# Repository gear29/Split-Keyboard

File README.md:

# Split-Keyboard
This is a key board  but 2
firm ware https://github.com/gear29/wireless-split-keyboard-firmware

 Wireless Split Keyboard

A custom wireless split mechanical keyboard powered by two Seeed Studio XIAO nRF52840 controllers and ZMK firmware.

Project Overview

Wireless Split Keyboard is a custom split keyboard designed around two independently powered wireless halves. Each half uses a Seeed Studio XIAO nRF52840 microcontroller and communicates using ZMK's split keyboard functionality.

The goal of this project is to create a fully custom keyboard, including its PCB, firmware, and mechanical design.

Features

Wireless split keyboard design

Two Seeed Studio XIAO nRF52840 controllers

ZMK firmware

Custom 5×5 matrix per half

42 total keys

Mechanical keyboard switches

Custom PCB design

Configurable keymap and layers

Repository Structure

wireless-split-keyboard/
├── README.md
├── bom.csv
├── PCB/
│   ├── schematic.kicad_sch
│   ├── pcb.kicad_pcb
│   └── gerbers/
├── CAD/
│   └── source-files/
└── Firmware/
    └── ZMK firmware repository

Building

Manufacture the custom PCB.

Assemble the keyboard electronics.

Flash the left and right ZMK firmware.

Configure and test the keyboard.

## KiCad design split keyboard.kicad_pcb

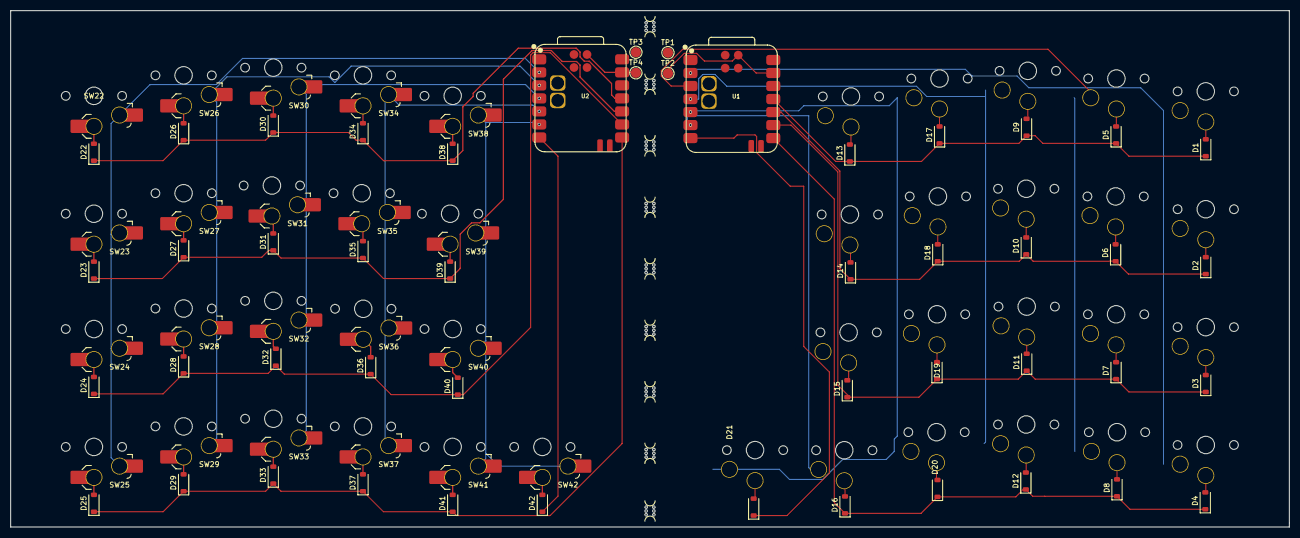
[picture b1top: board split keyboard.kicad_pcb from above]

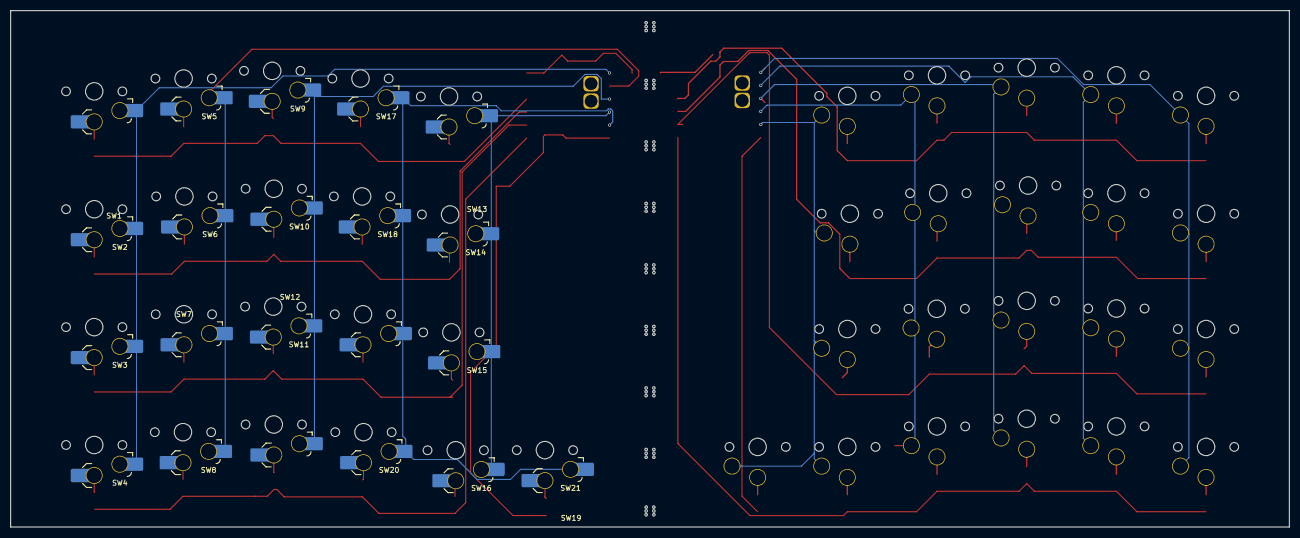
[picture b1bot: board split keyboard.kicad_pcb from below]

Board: 2 copper layers, 249.5 x 100.8 mm, 99 parts (21 on the bottom side), 64 nets.

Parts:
B1, B2, B3, B4, B5, B6, B8, B9, B10: MouseBite; mouse-bite-2mm-slot
D1, D2, D3, D4, D5, D6, D7, D8, D9, D10, D11, D12, D13, D14, D15, D16, D17, D18, D19, D20, D21, D22, D23, D24, D25, D26, D27, D28, D29, D30, D31, D32, D33, D34, D35, D36, D37, D38, D39, D40, D41, D42: D; D_SOD-123
SW1, SW2, SW3, SW4, SW5, SW6, SW7, SW8, SW9, SW10, SW11, SW12, SW13, SW14, SW15, SW16, SW17, SW18, SW19, SW20, SW21, SW22, SW23, SW24, SW25, SW26, SW27, SW28, SW29, SW30, SW31, SW32, SW33, SW34, SW35, SW36, SW37, SW38, SW39, SW40, SW41, SW42: SW_Push; SW_choc_v1_HS_CPG135001S30_1.5u
TP1, TP3: bat; TestPoint_Pad_D2.0mm
TP2, TP4: gnd; TestPoint_Pad_D2.0mm
U1, U2: XIAO-nRF52840-SMD; modified-XIAO-nRF52840-SMD

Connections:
/left(page 2)/C0L0: SW1.1, SW2.1, SW3.1, SW4.1, U1.2 (D1)
/left(page 2)/C0L1: SW5.1, SW6.1, SW7.1, SW8.1, U1.3 (D2)
/left(page 2)/C0L2: SW9.1, SW10.1, SW11.1, SW12.1, U1.4 (D3)
/left(page 2)/C0L3: SW13.1, SW14.1, SW15.1, SW16.1, U1.5 (D4)
/left(page 2)/C0L4: SW17.1, SW18.1, SW19.1, SW20.1, SW21.1, U1.6 (D5)
/left(page 2)/R0W0: D1.1 (K), D5.1 (K), D9.1 (K), D13.1 (K), D17.1 (K), U1.11 (D10)
/left(page 2)/R0W1: D2.1 (K), D6.1 (K), D10.1 (K), D14.1 (K), D18.1 (K), U1.10 (D9)
/left(page 2)/R0W2: D3.1 (K), D7.1 (K), D11.1 (K), D15.1 (K), D19.1 (K), U1.9 (D8)
/left(page 2)/R0W3: D4.1 (K), D8.1 (K), D12.1 (K), D16.1 (K), D20.1 (K), U1.8 (D7)
/left(page 2)/R0W4: D21.1 (K), U1.7 (D6)
/right/C0L0: SW22.1, SW23.1, SW24.1, SW25.1, U2.2 (D1)
/right/C0L1: SW26.1, SW27.1, SW28.1, SW29.1, U2.3 (D2)
/right/C0L2: SW30.1, SW31.1, SW32.1, SW33.1, U2.4 (D3)
/right/C0L3: SW34.1, SW35.1, SW36.1, SW37.1, U2.5 (D4)
/right/C0L4: SW38.1, SW39.1, SW40.1, SW41.1, SW42.1, U2.6 (D5)
/right/R0W0: D22.1 (K), D26.1 (K), D30.1 (K), D34.1 (K), D38.1 (K), U2.11 (D10)
/right/R0W1: D23.1 (K), D27.1 (K), D31.1 (K), D35.1 (K), D39.1 (K), U2.10 (D9)
/right/R0W2: D24.1 (K), D28.1 (K), D32.1 (K), D36.1 (K), D40.1 (K), U2.9 (D8)
/right/R0W3: D25.1 (K), D29.1 (K), D33.1 (K), D37.1 (K), D41.1 (K), U2.8 (D7)
/right/R0W4: D42.1 (K), U2.7 (D6)
GND: TP4.1 (1_1), U2.13 (GND), U2.20 (GND)
GND1: TP2.1 (1_1), U1.13 (GND), U1.20 (GND)
unnamed: D1.2 (A), SW1.2
unnamed: D2.2 (A), SW2.2
unnamed: D3.2 (A), SW3.2
unnamed: D4.2 (A), SW4.2
unnamed: D5.2 (A), SW5.2
unnamed: D6.2 (A), SW6.2
unnamed: D7.2 (A), SW7.2
unnamed: D8.2 (A), SW8.2
unnamed: D9.2 (A), SW9.2
unnamed: D10.2 (A), SW10.2
unnamed: D11.2 (A), SW11.2
unnamed: D12.2 (A), SW12.2
unnamed: D13.2 (A), SW13.2
unnamed: D14.2 (A), SW14.2
unnamed: D15.2 (A), SW15.2
unnamed: D16.2 (A), SW16.2
unnamed: D17.2 (A), SW17.2
unnamed: D18.2 (A), SW18.2
unnamed: D19.2 (A), SW19.2
unnamed: D20.2 (A), SW20.2
unnamed: D21.2 (A), SW21.2
unnamed: D22.2 (A), SW22.2
unnamed: D23.2 (A), SW23.2
unnamed: D24.2 (A), SW24.2
unnamed: D25.2 (A), SW25.2
unnamed: D26.2 (A), SW26.2
unnamed: D27.2 (A), SW27.2
unnamed: D28.2 (A), SW28.2
unnamed: D29.2 (A), SW29.2
unnamed: D30.2 (A), SW30.2
unnamed: D31.2 (A), SW31.2
unnamed: D32.2 (A), SW32.2
unnamed: D33.2 (A), SW33.2
unnamed: D34.2 (A), SW34.2
unnamed: D35.2 (A), SW35.2
unnamed: D36.2 (A), SW36.2
unnamed: D37.2 (A), SW37.2
unnamed: D38.2 (A), SW38.2
unnamed: D39.2 (A), SW39.2
unnamed: D40.2 (A), SW40.2
unnamed: D41.2 (A), SW41.2
unnamed: D42.2 (A), SW42.2
